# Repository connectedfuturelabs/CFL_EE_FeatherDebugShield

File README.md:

# Description
- This is a SWD breakout shield for the Feather M0 and a JTAG breakout shield for Feather ESP32.
- The Feather M0 has a provision for SWD debugging which requires soldering leads to the SWD pads on the bottom on the Feather M0. We made this shield so that we can debug a Feather M0 without having to solder leads. Instead, we use pogo pins to create the contact when the feather M0 is stacked on this shield.
- The Feather ESP32 can be debugged using the JTAG interface. This shield has a provision for debugging with ESP32 using solder bridges to create the necessary connections. **This configuration has not been tested.**

## Debug shield
**Note that this is a bare bones board (which is why the SM and silk screen are missing)**

| stage | how it looks |
|-------|----------|
| After fabrication |  |
| After Assembly |  |
| Stacked with a Feather |  |
| Stacked with Feather and [EmotiBit](https://www.emotibit.com/) |  |

# Using this repository
- The latest release contains all files required for creating the board.
- To fabricate this board
  - Download the `.zip` from the release page.
  - The files needed for manufacturing are in the `Gerbers` folder.
  - Just upload the gerber design files on a manufacturer's website and choose other board specifications.
  - We used [`4PCB`](https://www.4pcb.com/pcb-prototype-2-4-layer-boards-specials.html) as our manufacturer.
  - The `_bom.csv` file contains the parts needed for assembly. You can directly upload the bom file into the digikey portal to get the required parts for assembly.
- Once the shield is fabbed and stacked, you can use the [10 pin JTAG conector cable](https://www.digikey.com/en/products/detail/olimex-ltd/ARM-JTAG-20-10/3471401?utm_adgroup=&utm_source=google&utm_medium=cpc&utm_campaign=PMax%20Shopping_Product_Low%20ROAS%20Categories&utm_term=&utm_content=&utm_id=go_cmp-20243063506_adg-_ad-__dev-c_ext-_prd-3471401_sig-CjwKCAiAmsurBhBvEiwA6e-WPNh5BHwkzxviOyLhfwEuieJADaysFQ4kxIkHNQBExya359XoMJ5D-hoCkgkQAvD_BwE&gad_source=1&gclid=CjwKCAiAmsurBhBvEiwA6e-WPNh5BHwkzxviOyLhfwEuieJADaysFQ4kxIkHNQBExya359XoMJ5D-hoCkgkQAvD_BwE) to connecto to a [J-Link debugger](https://www.segger.com/products/debug-probes/j-link/).

## Assembly notes
- It is important to line up the pogo pins vertically to ensure there is a contact with the pads on the Feather. The following sequence helps with the allignment:
  - solder the 12 and 16 pin connector.
  - place the pogo pins in the correct position
  - stack the Feather on the shield.
  - then align the pogo pins with a pair of tweezers to ensure contact.
  - solder the pins in place
- We used stacking headers because we intend to use this as a triple stack with EmotiBit, but if you are only interested in debugging the Feather, then you can use normal female socket for the connector. 

# Additional Notes
- The design was created in Kicad 7.
- If you want to build on top of this design, please feel free to fork the repository and make the rewuired changes! you will need to download Kicad v7+ to work with the design files.

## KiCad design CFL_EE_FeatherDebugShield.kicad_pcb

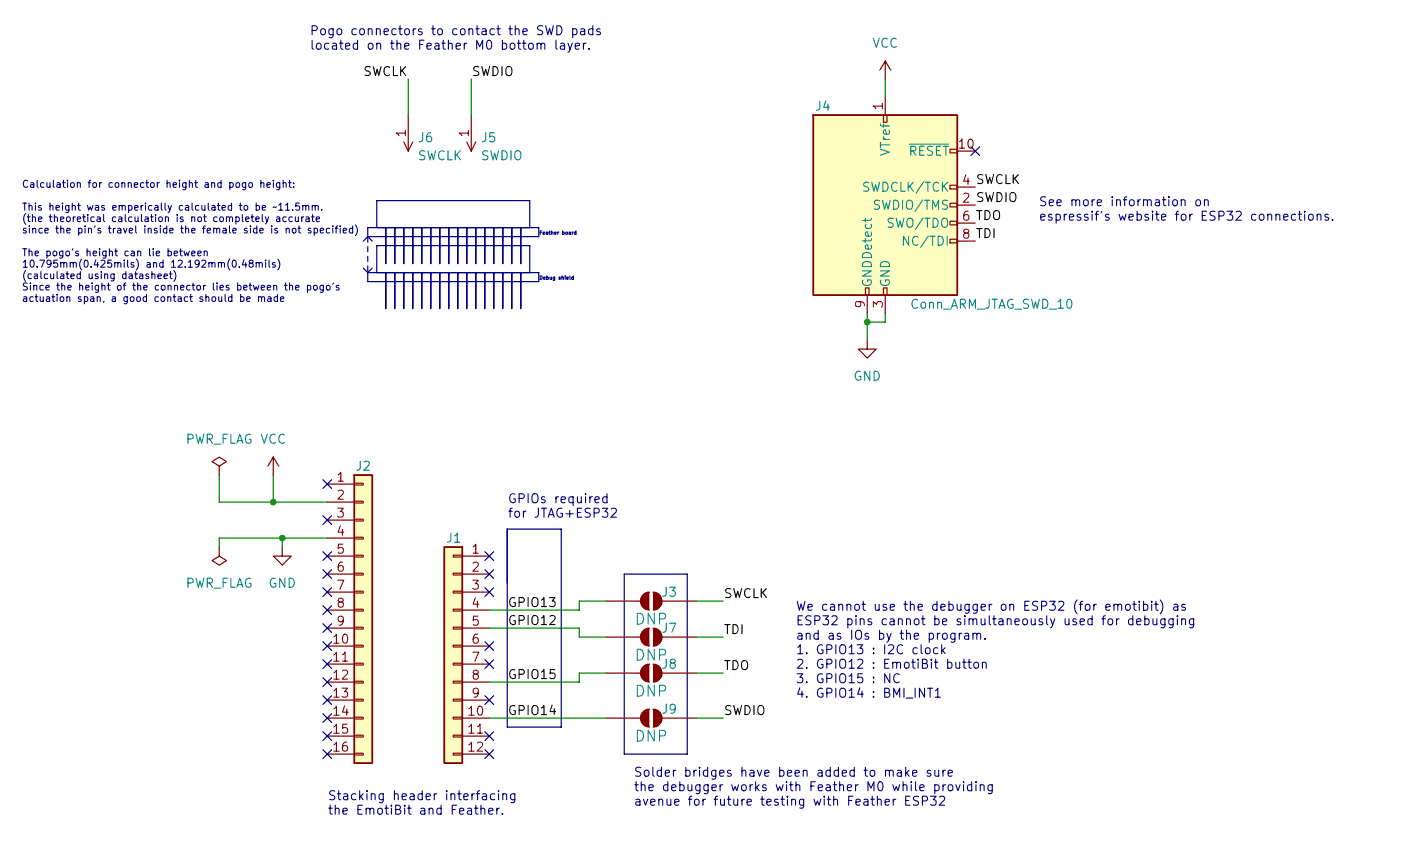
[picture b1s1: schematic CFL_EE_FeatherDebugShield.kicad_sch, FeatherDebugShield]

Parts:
J1: Conn_01x12; PinSocket_1x12_P2.54mm_Vertical; MPN SSQ-112-03-G-S
J2: Conn_01x16; PinSocket_1x16_P2.54mm_Vertical; MPN SSQ-116-03-G-S
J3, J7, J8, J9: CONN_JUMPER_NO; CONN_SLDR_BRDG_NO
J4: Conn_ARM_JTAG_SWD_10; SAMTEC_FTSH-105-01-F-DV-K-TR; MPN FTSH-105-01-F-DV-K-P
J5: SWDIO; CONN_PROBE_SPRING_01X01_C150H75; MPN 0929-7-15-20-75-14-11-0
J6: SWCLK; CONN_PROBE_SPRING_01X01_C150H75; MPN 0929-7-15-20-75-14-11-0

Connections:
/GPIO12: J1.5, J7.1
/GPIO13: J1.4, J3.1
/GPIO14: J1.10, J9.1
/GPIO15: J1.8, J8.1
/SWCLK: J3.2, J4.4 (SWDCLK/TCK), J6.1
/SWDIO: J4.2 (SWDIO/TMS), J5.1, J9.2
/TDI: J4.8 (NC/TDI), J7.2
/TDO: J4.6 (SWO/TDO), J8.2
GND: J2.4, J4.3 (GND), J4.5 (GND), J4.9 (GNDDetect)
VCC: J2.2, J4.1 (VTref)

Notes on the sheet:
Stacking header interfacing the EmotiBit and Feather.
Debug shield
See more information on espressif's website for ESP32 connections.
Pogo connectors to contact the SWD pads located on the Feather M0 bottom layer.
We cannot use the debugger on ESP32 (for emotibit) as ESP32 pins cannot be simultaneously used for debugging and as IOs by the program. 1. GPIO13 : I2C clock 2. GPIO12 : EmotiBit button 3. GPIO15 : NC 4. GPIO14 : BMI_INT1
Feather board
GPIOs required for JTAG+ESP32
Calculation for connector height and pogo height: This height was emperically calculated to be ~11.5mm. (the theoretical calculation is not completely accurate since the pin's travel inside the female side is not specified) The pogo's height can lie between 10.795mm(0.425mils) and 12.192mm(0.48mils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
Solder bridges have been added to make sure the debugger works with Feather M0 while providing avenue for future testing with Feather ESP32

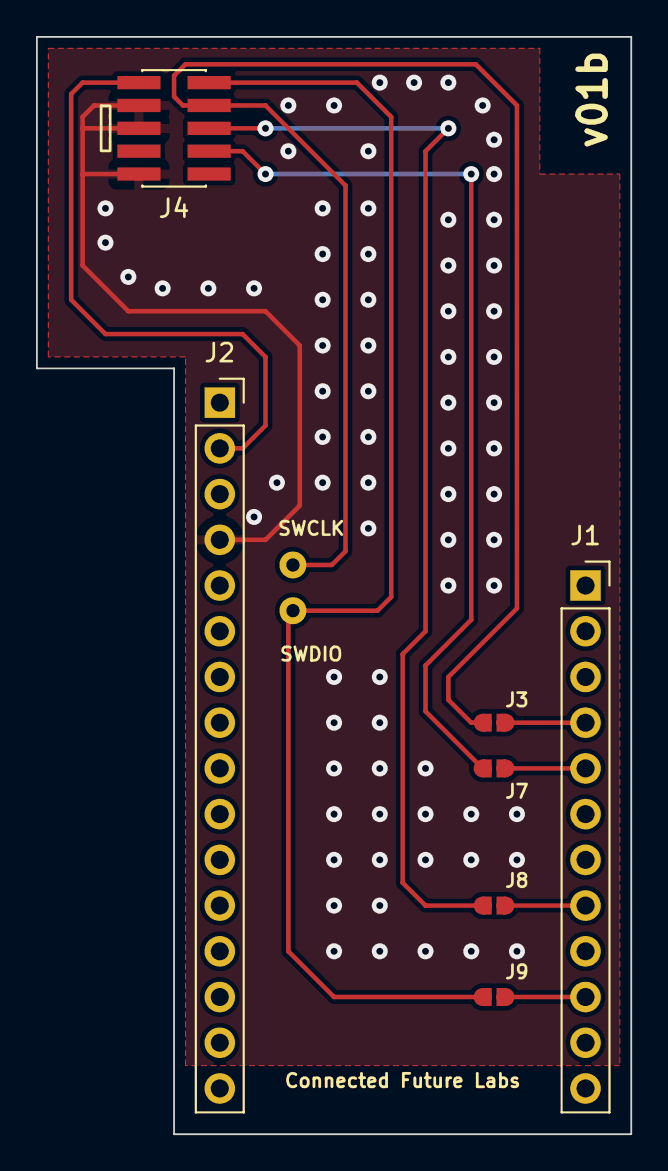
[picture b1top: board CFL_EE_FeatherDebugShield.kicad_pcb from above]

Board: 2 copper layers, 33.0 x 61.0 mm, 9 parts (0 on the bottom side), 10 nets.

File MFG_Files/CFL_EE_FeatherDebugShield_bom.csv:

Component,Description,Part,References,Value,Footprint,Quantity Per PCB,Datasheet,Config,Land Pattern,MPN,Manufacturer,Max height,Mounting Type,Supplier 1,Supplier 1 Link,Supplier 1 Part Number
1,"Generic connector, single row, 01x12, script generated (kicad-library-utils/schlib/autogen/connector/)",Conn_01x12,J1,Conn_01x12,PinSocket_1x12_P2.54mm_Vertical,1,https://suddendocs.samtec.com/catalog_english/ssq_th.pdf,,https://suddendocs.samtec.com/prints/ssq-1xx-xx-xx-x-xx-xxx-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,SSQ-112-03-G-S,Samtec Inc.,8.61mm,Through hole,Digikey,https://www.digikey.com/en/products/detail/samtec-inc/SSQ-11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,SAM1198-12-ND
2,"Generic connector, single row, 01x16, script generated (kicad-library-utils/schlib/autogen/connector/)",Conn_01x16,J2,Conn_01x16,PinSocket_1x16_P2.54mm_Vertical,1,https://suddendocs.samtec.com/catalog_english/ssq_th.pdf,,https://suddendocs.samtec.com/prints/ssq-1xx-xx-xx-x-xx-xxx-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,SSQ-116-03-G-S,Samtec Inc.,8.61mm,Through Hole,Digikey,https://www.digikey.com/en/products/detail/samtec-inc/SSQ-11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,SAM1198-16-ND
3,"Cortex Debug Connector, standard ARM Cortex-M SWD and JTAG interface",Conn_ARM_JTAG_SWD_10,J4,Conn_ARM_JTAG_SWD_10,SAMTEC_FTSH-105-01-F-DV-K-TR,1,http://infocenter.arm.com/help/topic/com.arm.doc.ddi0314h/DD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,,https://suddendocs.samtec.com/prints/ftsh-1xx-xx-xxx-dv-xxx-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,FTSH-105-01-F-DV-K-P,Samtec Inc.,,SMD,Digikey,https://www.digikey.com/en/products/detail/samtec-inc./FTSH-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,SAM8797-ND
4,CONTACT SPRING LOADED T/H GOLD,CONN_PROBE_SPRING_01X01_TH,J6,SWCLK,CONN_PROBE_SPRING_01X01_C150H75,1,https://www.mill-max.com/catalog/download/2020-03%3A025M.pdf,,DNF,0929-7-15-20-75-14-11-0,Mill-Max Manufacturing Corp.,12.2mm,Sureface Mount,DigiKey,https://www.digikey.com/en/products/detail/mill-max-manufact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,ED1420-ND
5,CONTACT SPRING LOADED T/H GOLD,CONN_PROBE_SPRING_01X01_TH,J5,SWDIO,CONN_PROBE_SPRING_01X01_C150H75,1,https://www.mill-max.com/catalog/download/2020-03%3A025M.pdf,,DNF,0929-7-15-20-75-14-11-0,Mill-Max Manufacturing Corp.,12.2mm,Sureface Mount,DigiKey,https://www.digikey.com/en/products/detail/mill-max-manufact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,ED1420-ND





Component Groups:,6
Component Count:,9
Fitted Components:,5
Number of PCBs:,1
Total components:,5
Schematic Version:,v01a
Schematic Date:,2023-10-23
PCB Variant:,default
BoM Date:,10/23/2023 11:08:31 AM
Schematic Source:,CFL_FeatherDebugShield.kicad_sch
KiCad Version:,Eeschema 7.0.6

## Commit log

2023-10-23 adding v01a files
2023-11-11 minor mods sch and pcb. version bump to v01b
2023-11-11 adding MFG files
2023-11-11 updated readme. added assets
2023-11-11 minor readme update
2023-11-11 adding bom file
2023-12-08 Adding stl for 3d seembly
2023-12-08 adding image of 3D model
